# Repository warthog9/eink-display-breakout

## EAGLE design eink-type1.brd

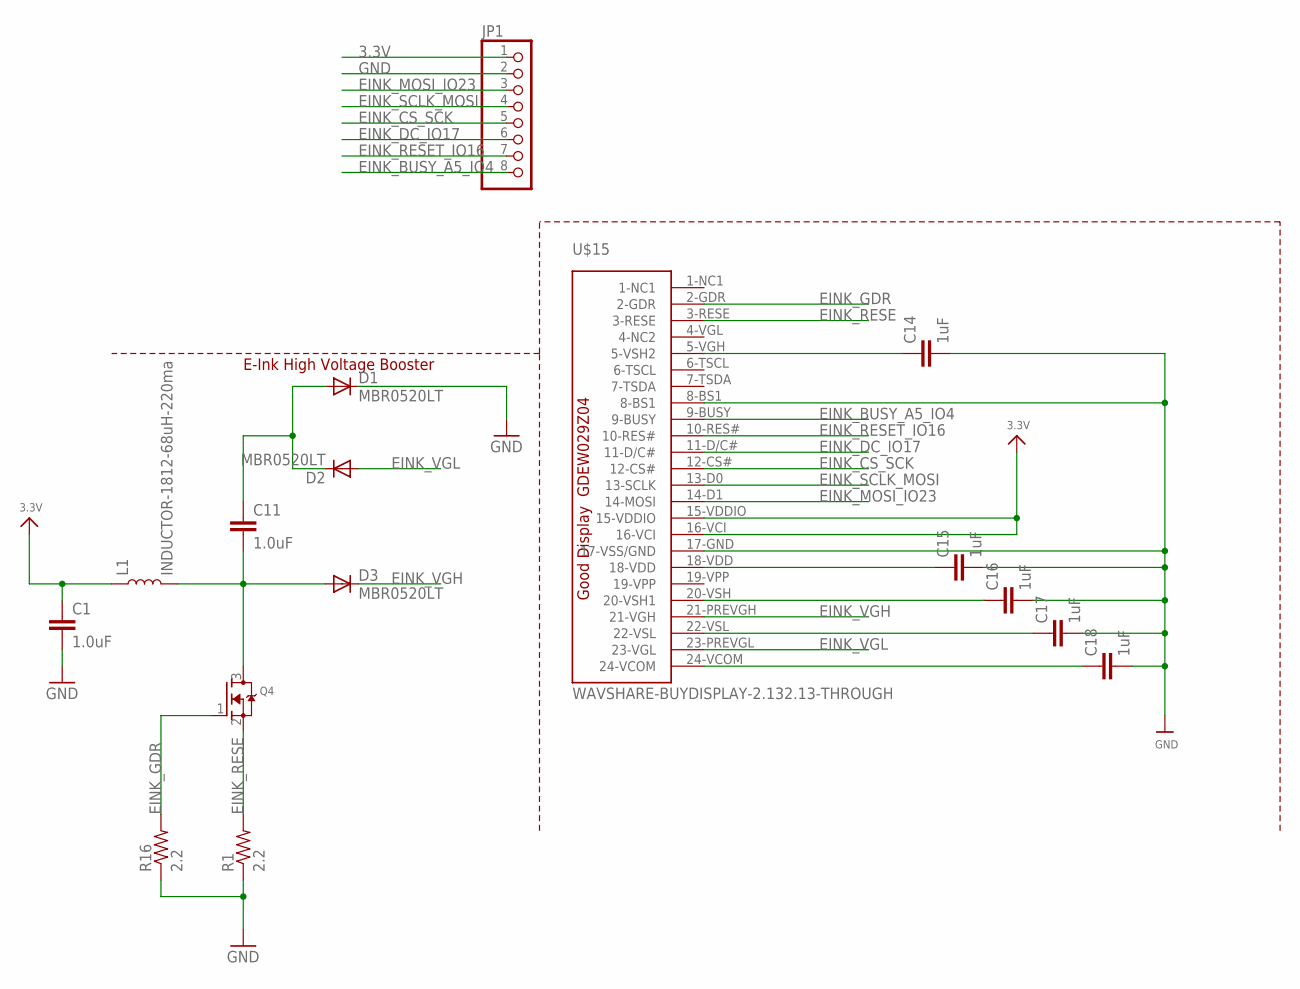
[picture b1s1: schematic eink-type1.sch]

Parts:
C1, C11: 1.0uF; 0603
C14, C15, C16, C17, C18: 1uF; 0603-CAP
D1, D2, D3: MBR0520LT; SOD123
JP1: PINHD-1X8; 1X08
L1: INDUCTOR-1812-68uH-220ma; 1812
Q4: MOSFET-NREFLOW; SOT23
R1, R16: 2.2; 0603-RES
U$15: WAVSHARE-BUYDISPLAY-2.132.13-THROUGH; WAVSHARE-BUYDISPLAY-2.13-THM

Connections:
3.3V: C1.1, JP1.1, L1.1, U$15.15-VDDIO, U$15.16-VCI
EINK_BUSY_A5_IO4: JP1.8, U$15.9-BUSY
EINK_CS_SCK: JP1.5, U$15.12-CS#
EINK_DC_IO17: JP1.6, U$15.11-D/C#
EINK_GDR: Q4.1 (G), R16.2, U$15.2-GDR
EINK_MOSI_IO23: JP1.3, U$15.14-D1 (14-MOSI)
EINK_RESE: Q4.2 (S), R1.2, U$15.3-RESE
EINK_RESET_IO16: JP1.7, U$15.10-RES#
EINK_SCLK_MOSI: JP1.4, U$15.13-D0 (13-SCLK)
EINK_VGH: D3.C, U$15.21-PREVGH (21-VGH)
EINK_VGL: D2.A, U$15.23-PREVGL (23-VGL)
GND: C1.2, C14.2, C15.2, C16.2, C17.2, C18.2, D1.C, JP1.2, R1.1, R16.1, U$15.8-BS1, U$15.17-GND (17-VSS/GND)
unnamed: C11.2, D3.A, L1.2, Q4.3 (D)
unnamed: C11.1, D1.A, D2.C
unnamed: C15.1, U$15.18-VDD
unnamed: C16.1, U$15.20-VSH (20-VSH1)
unnamed: C17.1, U$15.22-VSL
unnamed: C18.1, U$15.24-VCOM
unnamed: C14.1, U$15.5-VGH (5-VSH2)

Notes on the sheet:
E-Ink High Voltage Booster

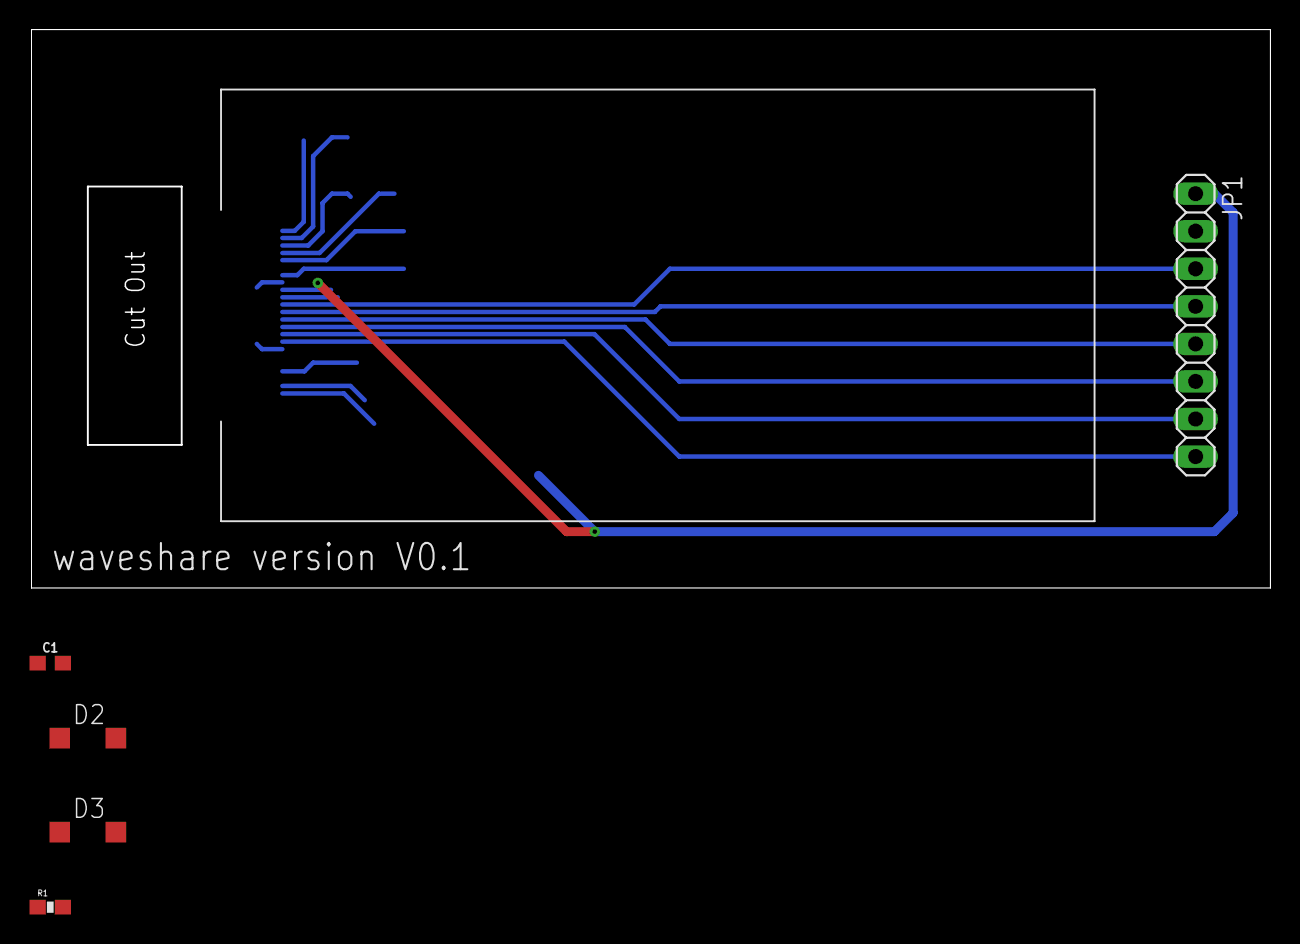
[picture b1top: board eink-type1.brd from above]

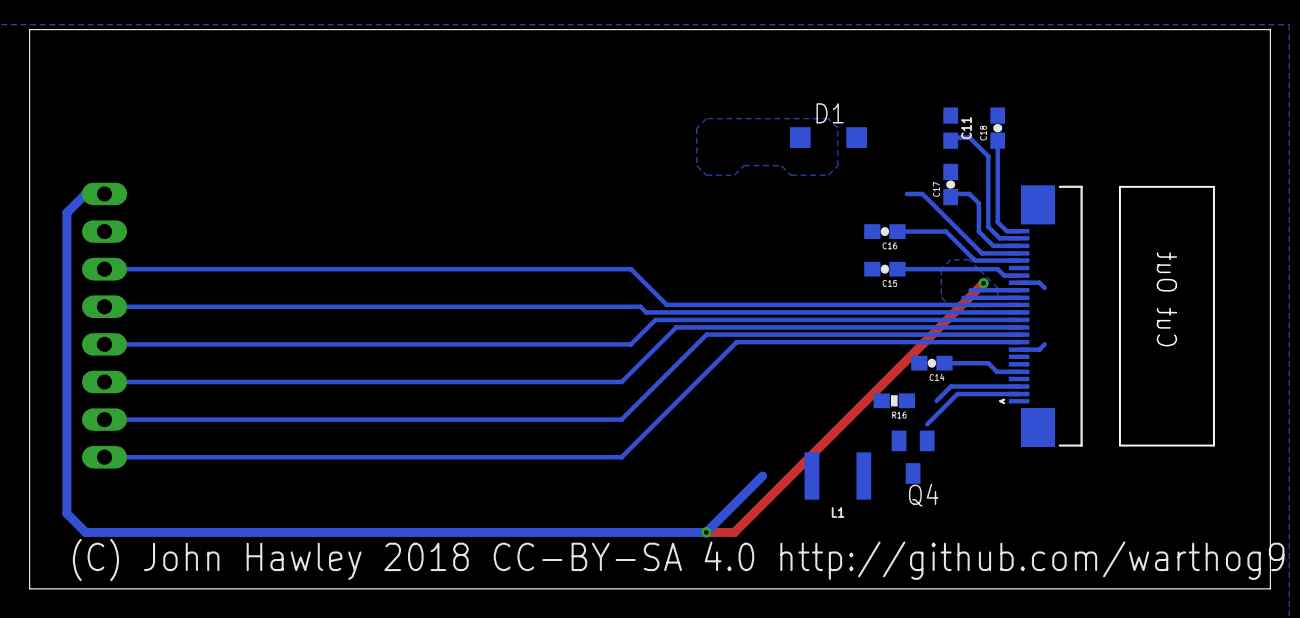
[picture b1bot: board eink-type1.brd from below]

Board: 2 copper layers, 83.7 x 37.6 mm, 16 parts (10 on the bottom side), 19 nets.

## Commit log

2020-08-08 Trinket circuit of the e-ink board
    This pretty much copies the schematic information from the Trinket
2020-08-08 Waveshare circuit of the e-ink board
    This pretty much copies the schematic information from Waveshare's
    documentation

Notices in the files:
eink-type1.brd:
(C) John Hawley 2018 CC-BY-SA 4.0 http://github.com/warthog9
parts and their libraries:
SparkFun-Capacitors: Licensing: Creative Commons ShareAlike 4.0 International - https://creativecommons.org/licenses/by-sa/4.0
microbuilder: This work is placed in the public domain, and may be freely used for commercial and non-commercial work with the following conditions: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
